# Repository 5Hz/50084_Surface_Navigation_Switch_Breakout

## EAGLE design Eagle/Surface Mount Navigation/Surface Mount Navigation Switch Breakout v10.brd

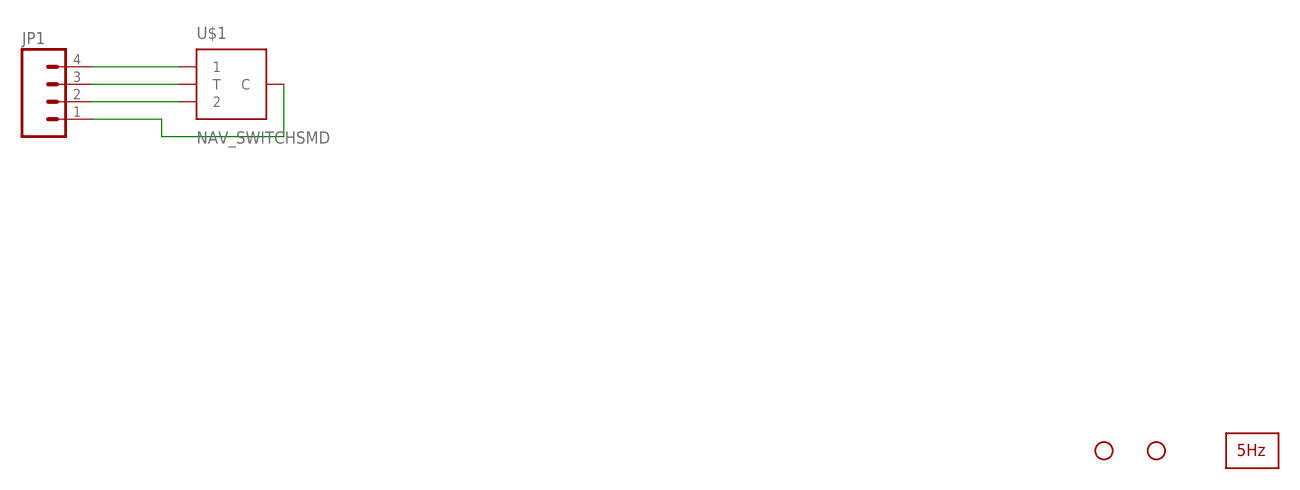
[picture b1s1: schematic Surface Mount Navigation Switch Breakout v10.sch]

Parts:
JP1: M04PTH; 1X04
JP2, JP3: STAND-OFF
U$1: NAV_SWITCHSMD; NAV_SWITCH
U$2: LOGO2_SILK5MM; LOGO2_5MM

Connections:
unnamed: JP1.4, U$1.1
unnamed: JP1.3, U$1.T
unnamed: JP1.2, U$1.2
unnamed: JP1.1, U$1.C

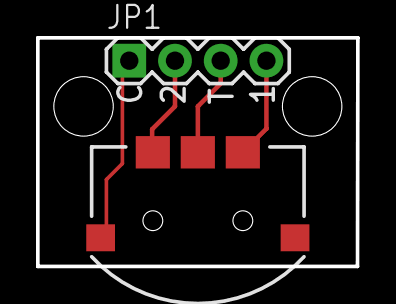
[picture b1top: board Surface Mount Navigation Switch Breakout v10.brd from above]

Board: 2 copper layers, 17.8 x 12.7 mm, 5 parts (1 on the bottom side), 4 nets.

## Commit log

2014-01-13 creación

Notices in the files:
parts and their libraries:
SparkFun: Licensing: CC v3.0 Share-Alike You are welcome to use this library for commercial purposes.
